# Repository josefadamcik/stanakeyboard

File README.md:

# sofleunsplit

WIP DIY keyboard design.

* Sofle V2 layout
* But Kailh Chock with 18x17 spacing, socketed
* one board, one micro
* WaveShare RP2040
* no PCB plates -> case is going to be 3d printed/lasercut or something
* no RGB support

## Requirements

* Uses symbols/footprints from https://github.com/zzeneg/zzkeeb

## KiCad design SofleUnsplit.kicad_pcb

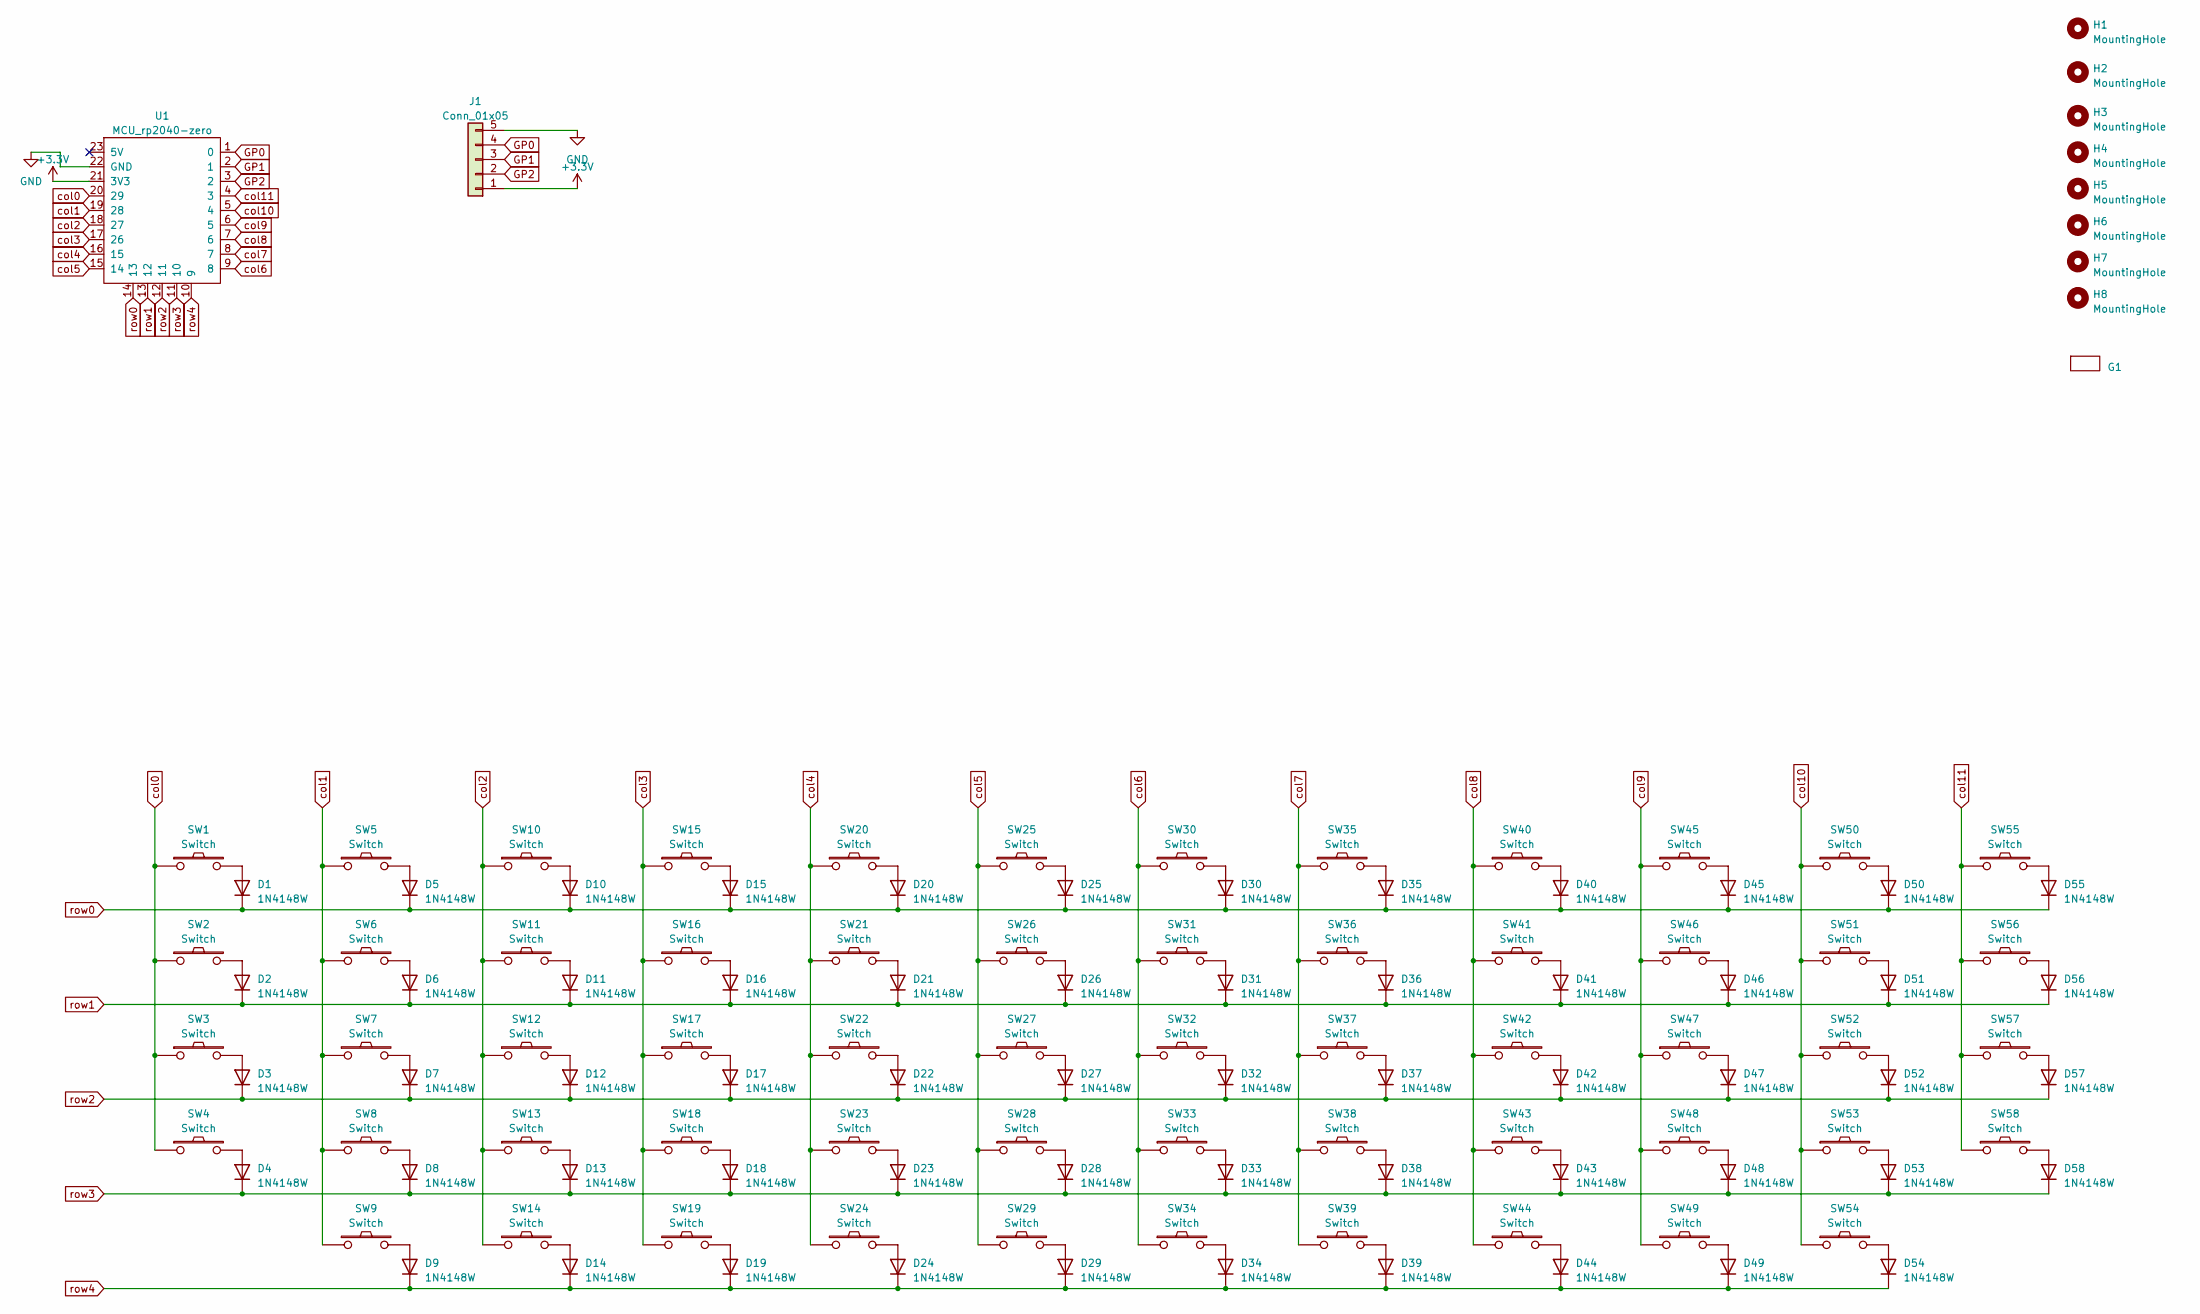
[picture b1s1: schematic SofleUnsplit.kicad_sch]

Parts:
D1, D2, D3, D4, D5, D6, D7, D8, D9, D10, D11, D12, D13, D14, D15, D16, D17, D18, D19, D20, D21, D22, D23, D24, D25, D26, D27, D28, D29, D30, D31, D32, D33, D34, D35, D36, D37, D38, D39, D40, D41, D42, D43, D44, D45, D46, D47, D48, D49, D50, D51, D52, D53, D54, D55, D56, D57, D58: 1N4148W; D_SOD-123F
G1: josef_adamcik_20mm_cu_mask
H1, H2, H3, H4: MountingHole; MountingHole_2.7mm_M2.5_DIN965
H5, H6, H7, H8: MountingHole; MountingHole_3.2mm_M3_DIN965
J1: Conn_01x05; PinSocket_1x05_P2.54mm_Vertical
SW1, SW2, SW3, SW4, SW5, SW6, SW7, SW8, SW9, SW10, SW11, SW12, SW13, SW14, SW15, SW16, SW17, SW18, SW19, SW20, SW21, SW22, SW23, SW24, SW25, SW26, SW27, SW28, SW29, SW30, SW31, SW32, SW33, SW34, SW35, SW36, SW37, SW38, SW39, SW40, SW41, SW42, SW43, SW44, SW45, SW46, SW47, SW48, SW49, SW50, SW51, SW52, SW53, SW54, SW55, SW56, SW57, SW58: Switch; Switch_ChocV1-hotswap
U1: MCU_rp2040-zero; MCU_rp2040-zero-smd

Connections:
+3.3V: J1.1, U1.21 (3V3)
GND: J1.5, U1.22 (GND)
GP0: J1.4, U1.1 (0)
GP1: J1.3, U1.2 (1)
GP2: J1.2, U1.3 (2)
unnamed: D1.2 (A), SW1.2
unnamed: D2.2 (A), SW2.2
unnamed: D3.2 (A), SW3.2
unnamed: D4.2 (A), SW4.2
unnamed: D5.2 (A), SW5.2
unnamed: D6.2 (A), SW6.2
unnamed: D7.2 (A), SW7.2
unnamed: D8.2 (A), SW8.2
unnamed: D9.2 (A), SW9.2
unnamed: D10.2 (A), SW10.2
unnamed: D11.2 (A), SW11.2
unnamed: D12.2 (A), SW12.2
unnamed: D13.2 (A), SW13.2
unnamed: D14.2 (A), SW14.2
unnamed: D15.2 (A), SW15.2
unnamed: D16.2 (A), SW16.2
unnamed: D17.2 (A), SW17.2
unnamed: D18.2 (A), SW18.2
unnamed: D19.2 (A), SW19.2
unnamed: D20.2 (A), SW20.2
unnamed: D21.2 (A), SW21.2
unnamed: D22.2 (A), SW22.2
unnamed: D23.2 (A), SW23.2
unnamed: D24.2 (A), SW24.2
unnamed: D25.2 (A), SW25.2
unnamed: D26.2 (A), SW26.2
unnamed: D27.2 (A), SW27.2
unnamed: D28.2 (A), SW28.2
unnamed: D29.2 (A), SW29.2
unnamed: D30.2 (A), SW30.2
unnamed: D31.2 (A), SW31.2
unnamed: D32.2 (A), SW32.2
unnamed: D33.2 (A), SW33.2
unnamed: D34.2 (A), SW34.2
unnamed: D35.2 (A), SW35.2
unnamed: D36.2 (A), SW36.2
unnamed: D37.2 (A), SW37.2
unnamed: D38.2 (A), SW38.2
unnamed: D39.2 (A), SW39.2
unnamed: D40.2 (A), SW40.2
unnamed: D41.2 (A), SW41.2
unnamed: D42.2 (A), SW42.2
unnamed: D43.2 (A), SW43.2
unnamed: D44.2 (A), SW44.2
unnamed: D45.2 (A), SW45.2
unnamed: D46.2 (A), SW46.2
unnamed: D47.2 (A), SW47.2
unnamed: D48.2 (A), SW48.2
unnamed: D49.2 (A), SW49.2
unnamed: D50.2 (A), SW50.2
unnamed: D51.2 (A), SW51.2
unnamed: D52.2 (A), SW52.2
unnamed: D53.2 (A), SW53.2
unnamed: D54.2 (A), SW54.2
unnamed: D55.2 (A), SW55.2
unnamed: D56.2 (A), SW56.2
unnamed: D57.2 (A), SW57.2
unnamed: D58.2 (A), SW58.2
col0: SW1.1, SW2.1, SW3.1, SW4.1, U1.20 (29)
col1: SW5.1, SW6.1, SW7.1, SW8.1, SW9.1, U1.19 (28)
col2: SW10.1, SW11.1, SW12.1, SW13.1, SW14.1, U1.18 (27)
col3: SW15.1, SW16.1, SW17.1, SW18.1, SW19.1, U1.17 (26)
col4: SW20.1, SW21.1, SW22.1, SW23.1, SW24.1, U1.16 (15)
col5: SW25.1, SW26.1, SW27.1, SW28.1, SW29.1, U1.15 (14)
col6: SW30.1, SW31.1, SW32.1, SW33.1, SW34.1, U1.9 (8)
col7: SW35.1, SW36.1, SW37.1, SW38.1, SW39.1, U1.8 (7)
col8: SW40.1, SW41.1, SW42.1, SW43.1, SW44.1, U1.7 (6)
col9: SW45.1, SW46.1, SW47.1, SW48.1, SW49.1, U1.6 (5)
col10: SW50.1, SW51.1, SW52.1, SW53.1, SW54.1, U1.5 (4)
col11: SW55.1, SW56.1, SW57.1, SW58.1, U1.4 (3)
row0: D1.1 (K), D5.1 (K), D10.1 (K), D15.1 (K), D20.1 (K), D25.1 (K), D30.1 (K), D35.1 (K), D40.1 (K), D45.1 (K), D50.1 (K), D55.1 (K), U1.14 (13)
row1: D2.1 (K), D6.1 (K), D11.1 (K), D16.1 (K), D21.1 (K), D26.1 (K), D31.1 (K), D36.1 (K), D41.1 (K), D46.1 (K), D51.1 (K), D56.1 (K), U1.13 (12)
row2: D3.1 (K), D7.1 (K), D12.1 (K), D17.1 (K), D22.1 (K), D27.1 (K), D32.1 (K), D37.1 (K), D42.1 (K), D47.1 (K), D52.1 (K), D57.1 (K), U1.12 (11)
row3: D4.1 (K), D8.1 (K), D13.1 (K), D18.1 (K), D23.1 (K), D28.1 (K), D33.1 (K), D38.1 (K), D43.1 (K), D48.1 (K), D53.1 (K), D58.1 (K), U1.11 (10)
row4: D9.1 (K), D14.1 (K), D19.1 (K), D24.1 (K), D29.1 (K), D34.1 (K), D39.1 (K), D44.1 (K), D49.1 (K), D54.1 (K), U1.10 (9)

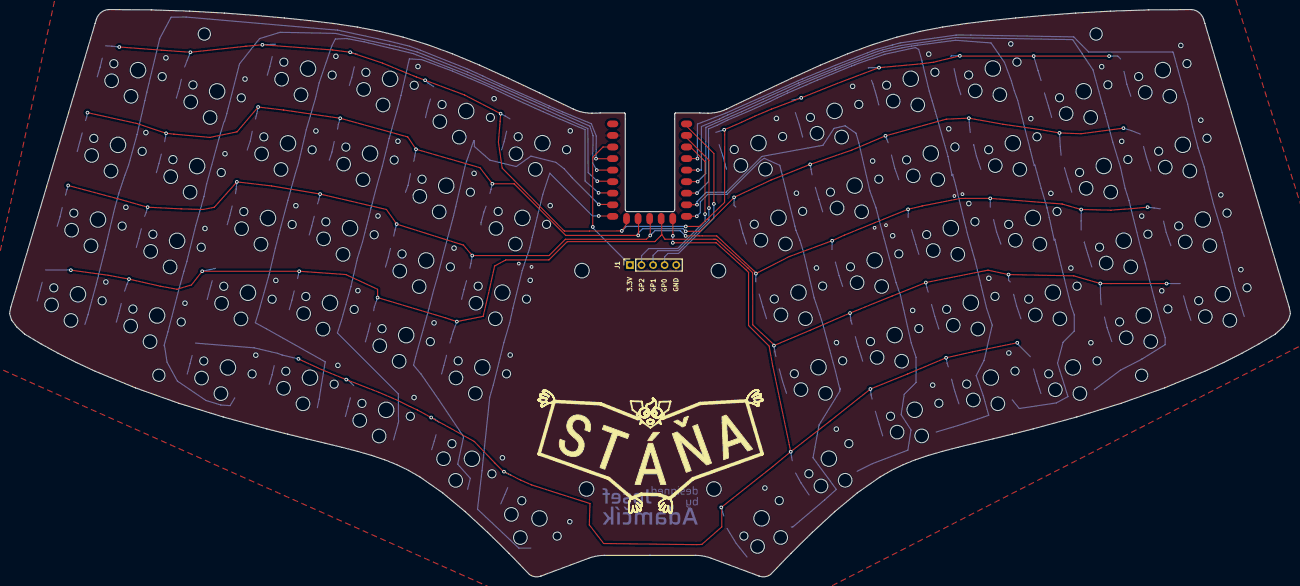
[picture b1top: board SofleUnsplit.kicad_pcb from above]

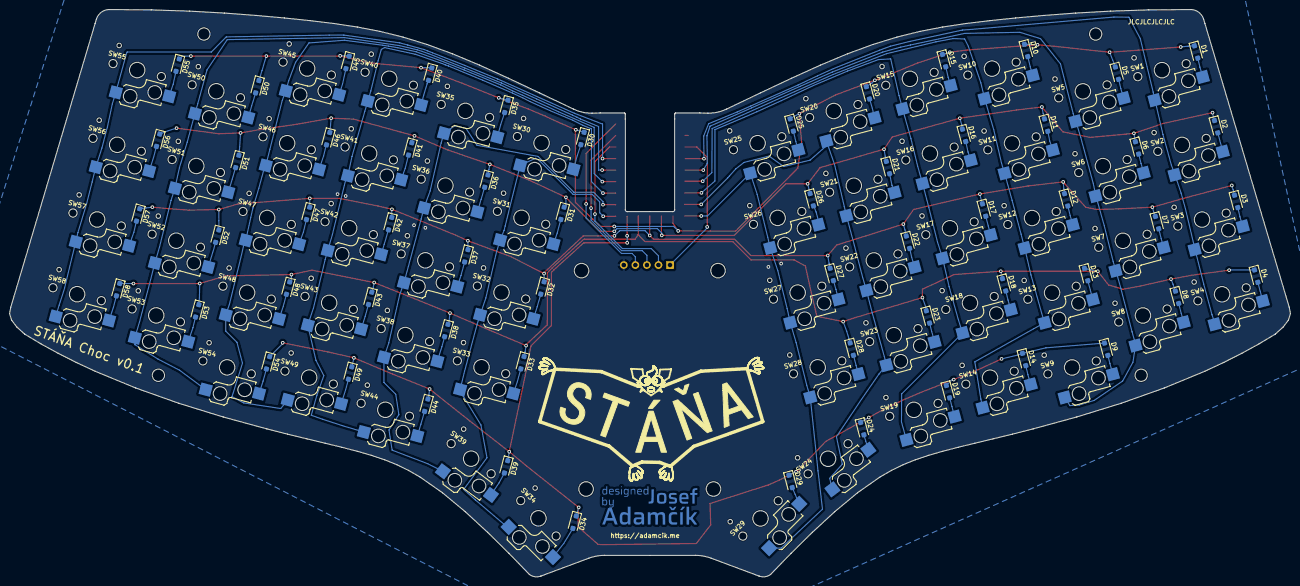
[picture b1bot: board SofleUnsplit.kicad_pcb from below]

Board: 2 copper layers, 281.5 x 124.7 mm, 127 parts (59 on the bottom side), 80 nets.

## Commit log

2023-03-23 Left half switches
2023-03-23 Both halves
2023-03-23 First version
2023-03-26 Improved shape in fusion360. Bit bigger and smooth curve.
2023-03-26 Place diodes differently
2023-03-26 Routing the right half WIP
2023-03-26 Right half routed
2023-03-26 Routing done
2023-03-26 Polishing, finishing
2023-03-26 Finalising
2023-03-26 First version, final, before last check.
2023-03-26 Add placement for JLCPCB number
2023-03-26 Minor fixes
2023-03-27 Ues SOD-123 layout for dioedes (might be easier to solder by hand than SOD-123F even though I have SOD-123F diodes). Logo as footprint in copper.
2023-03-27 Final changes
2023-03-28 some renames
2023-04-09 Minor things
2023-04-15 Iterating over case and logog
